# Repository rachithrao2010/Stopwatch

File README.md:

Hey!
So this is my stopwatch!
It uses cpp for the firmware, a custom case, and a PCB.
Here's a 3D render of the PCB:
You press the first to start it, the second to stop it, and the third to reset it! super simple stopwatch.

and here's a render of the case:

Here's the actual onshape link:
[https://cad.onshape.com/documents/91400ce87159a00817b7653b/w/000341720edffc3c094def40/e/c153008d87bc4e3ec63b634d](url)

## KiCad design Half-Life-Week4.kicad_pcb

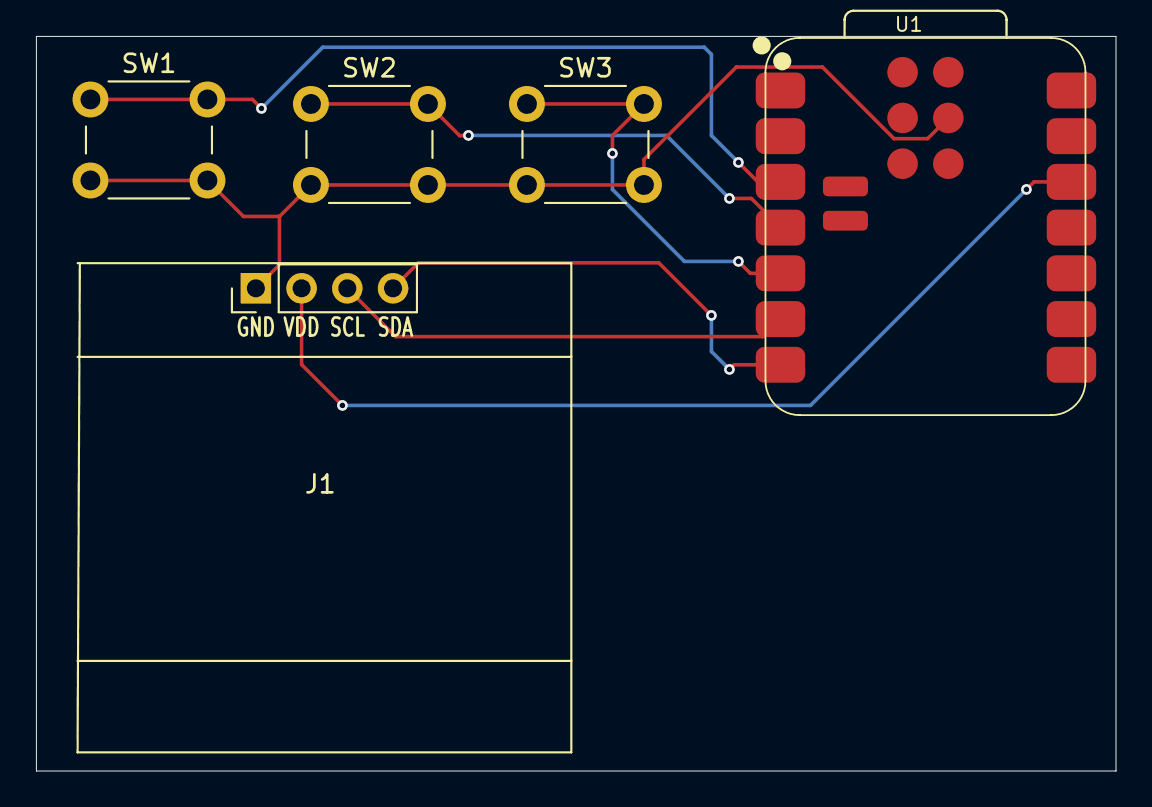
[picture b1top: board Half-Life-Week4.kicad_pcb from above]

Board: 2 copper layers, 60.0 x 40.8 mm, 5 parts (0 on the bottom side), 7 nets.

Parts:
J1: Conn_01x04_Pin; Display_128x64_096_I2C
SW1, SW2, SW3: SW_Push; SW_PUSH_6mm
U1: XIAO-ESP32-C3-SMD

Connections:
+3.3V: J1.2, U1.12 (3V3_OUT)
/GPIO1: SW1.1, U1.3 (D2)
/GPIO2: SW2.1, U1.4 (D3)
/GPIO3: SW3.1, U1.5 (D4)
/SCL: J1.3, U1.6 (D5)
/SDA: J1.4, U1.7 (D6)
GND: J1.1, SW1.2, SW2.2, SW3.2, U1.13 (GND), U1.18 (GND)
